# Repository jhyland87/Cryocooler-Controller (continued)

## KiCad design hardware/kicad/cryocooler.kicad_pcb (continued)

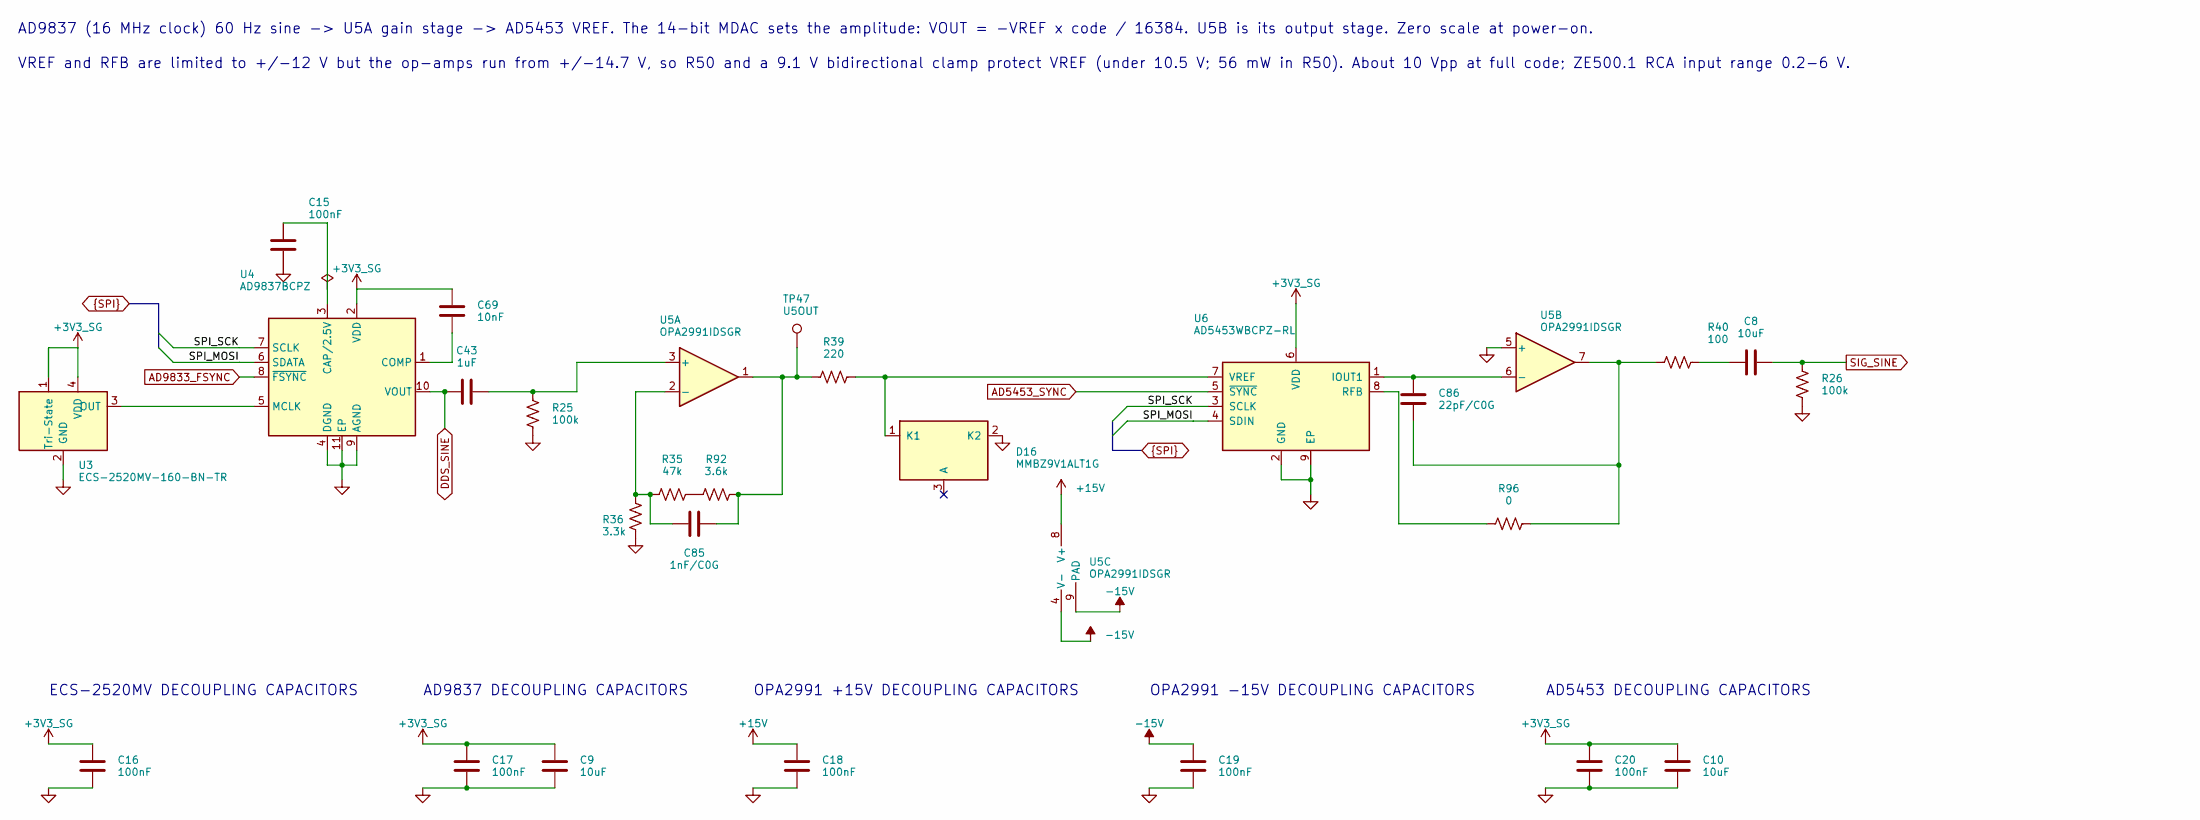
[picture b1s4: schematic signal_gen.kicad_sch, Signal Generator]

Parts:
C8, C9, C10: 10uF; C_0805_2012Metric
C15, C16, C17, C18, C19, C20: 100nF; C_0402_1005Metric
C43: 1uF; C_0603_1608Metric
C69: 10nF; C_0402_1005Metric
C85: 1nF/C0G; C_0402_1005Metric
C86: 22pF/C0G; C_0402_1005Metric
D16: MMBZ9V1ALT1G; SOT-23
R25, R26: 100k; R_0402_1005Metric
R35: 47k; R_0402_1005Metric
R36: 3.3k; R_0402_1005Metric
R39: 220; R_0402_1005Metric
R40: 100; R_0402_1005Metric
R92: 3.6k; R_1206_or_Bourns_3313J
R96: 0; R_1206_or_Bourns_3313J
TP47: U5OUT; TestPoint_Pad_D1.0mm
U3: ECS-2520MV-160-BN-TR; Oscillator_SMD_ECS_2520MV-xxx-xx-4Pin_2.5x2.0mm
U4: AD9837BCPZ; LFCSP-WD-10-1EP_3x3mm_P0.5mm_EP1.64x2.38mm
U5: OPA2991IDSGR; TI_DSG0008A_WSON-8-1EP_2x2mm_P0.5mm_EP0.9x1.6mm
U6: AD5453WBCPZ-RL; VSON-8-1EP_3x3mm_P0.65mm_EP1.65x2.4mm

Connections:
+3V3_SG: C9.1, C10.1, C16.1, C17.1, C20.1, C69.1, U3.1 (Tri-State), U3.4 (VDD), U4.2 (VDD), U6.6 (VDD); also elsewhere on the board
+15V: C18.1, U5.8 (V+); also elsewhere on the board
-15V: C19.1, U5.4 (V-), U5.9 (PAD); also elsewhere on the board
AD5453_SYNC: U6.5 (~SYNC); also elsewhere on the board
AD9833_FSYNC: U4.8 (~FSYNC); also elsewhere on the board
DDS_SINE: C43.1, U4.10 (VOUT); also elsewhere on the board
GND: C9.2, C10.2, C15.2, C16.2, C17.2, C18.2, C19.2, C20.2, D16.2 (K2), R25.2, R26.2, R36.2, U3.2 (GND), U4.4 (DGND), U4.9 (AGND), U4.11 (EP), U5.5 (+), U6.2 (GND), U6.9 (EP); also elsewhere on the board
unnamed: C8.1, R40.2
unnamed: C85.2, R39.1, R92.2, TP47.1, U5.1
unnamed: C86.2, R40.1, R96.2, U5.7
unnamed: D16.1 (K1), R39.2, U6.7 (VREF)
unnamed: R35.2, R92.1
unnamed: U3.3 (OUT), U4.5 (MCLK)
unnamed: C15.1, U4.3 (CAP/2.5V)
unnamed: C69.2, U4.1 (COMP)
unnamed: C43.2, R25.1, U5.3 (+)
unnamed: C85.1, R35.1, R36.1, U5.2 (-)
unnamed: C86.1, U5.6 (-), U6.1 (IOUT1)
unnamed: R96.1, U6.8 (RFB)
SIG_SINE: C8.2, R26.1; also elsewhere on the board
SPI_MOSI: U4.6 (SDATA), U6.4 (SDIN); also elsewhere on the board
SPI_SCK: U4.7 (SCLK), U6.3 (SCLK); also elsewhere on the board

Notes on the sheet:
ECS-2520MV DECOUPLING CAPACITORS
OPA2991 +15V DECOUPLING CAPACITORS
OPA2991 -15V DECOUPLING CAPACITORS
AD9837 DECOUPLING CAPACITORS
AD9837 (16 MHz clock) 60 Hz sine -> U5A gain stage -> AD5453 VREF. The 14-bit MDAC sets the amplitude: VOUT = -VREF x code / 16384. U5B is its output stage. Zero scale at power-on.
VREF and RFB are limited to +/-12 V but the op-amps run from +/-14.7 V, so R50 and a 9.1 V bidirectional clamp protect VREF (under 10.5 V; 56 mW in R50). About 10 Vpp at full code; ZE500.1 RCA input range 0.2-6 V.
AD5453 DECOUPLING CAPACITORS

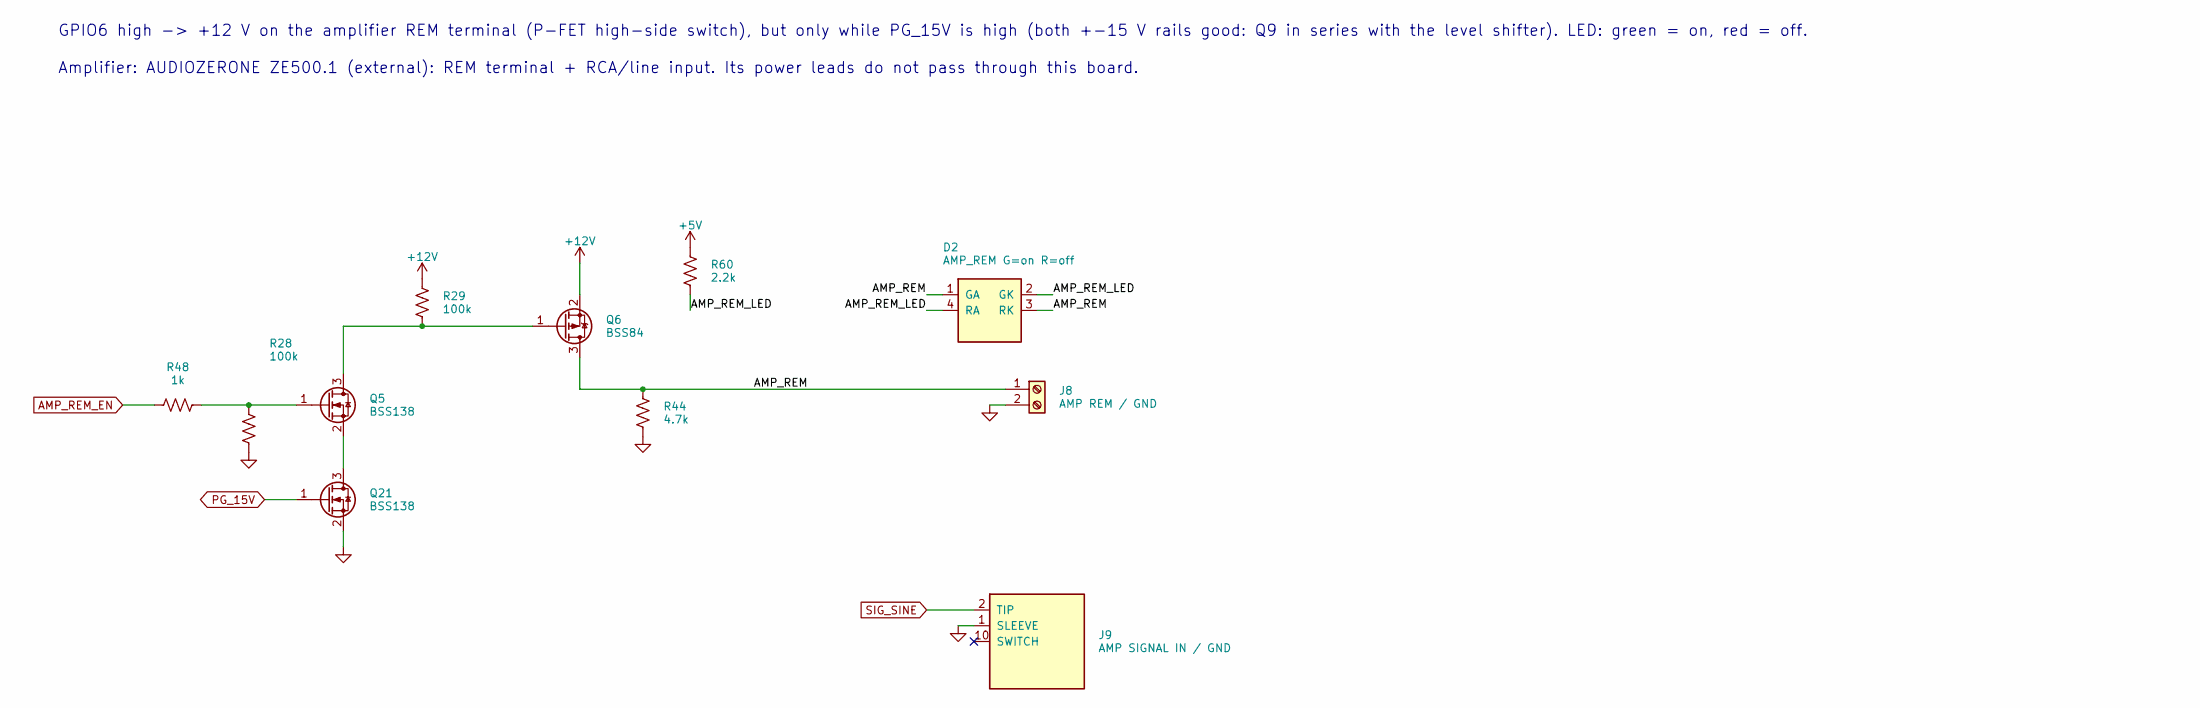
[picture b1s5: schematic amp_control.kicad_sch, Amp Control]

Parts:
D2: AMP_REM G=on R=off; LED_Kingbright_APGB0607
J8: AMP REM / GND; PhoenixContact_MC_0,5_2-G-2,54_SMD_1x02_P2.54mm_Horizontal
J9: AMP SIGNAL IN / GND; SameSky_MJ-3523-SMT-TR_3.5mm_Horizontal_SMD
Q5, Q21: BSS138; SOT-23
Q6: BSS84; SOT-23
R28, R29: 100k; R_0402_1005Metric
R44: 4.7k; R_0402_1005Metric
R48: 1k; R_0402_1005Metric
R60: 2.2k; R_0402_1005Metric

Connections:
+5V: R60.1; also elsewhere on the board
+12V: Q6.2 (S), R29.1; also elsewhere on the board
/Amp Control/AMP_REM: D2.1 (GA), D2.3 (RK), J8.1, Q6.3 (D), R44.1
/Amp Control/AMP_REM_LED: D2.2 (GK), D2.4 (RA), R60.2
AMP_REM_EN: R48.1; also elsewhere on the board
GND: J8.2, J9.1 (SLEEVE), Q21.2 (S), R28.2, R44.2; also elsewhere on the board
unnamed: Q5.3 (D), Q6.1 (G), R29.2
unnamed: Q5.1 (G), R28.1, R48.2
unnamed: Q5.2 (S), Q21.3 (D)
PG_15V: Q21.1 (G); also elsewhere on the board
SIG_SINE: J9.2 (TIP); also elsewhere on the board

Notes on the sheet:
GPIO6 high -> +12 V on the amplifier REM terminal (P-FET high-side switch), but only while PG_15V is high (both +-15 V rails good: Q9 in series with the level shifter). LED: green = on, red = off.
Amplifier: AUDIOZERONE ZE500.1 (external): REM terminal + RCA/line input. Its power leads do not pass through this board.

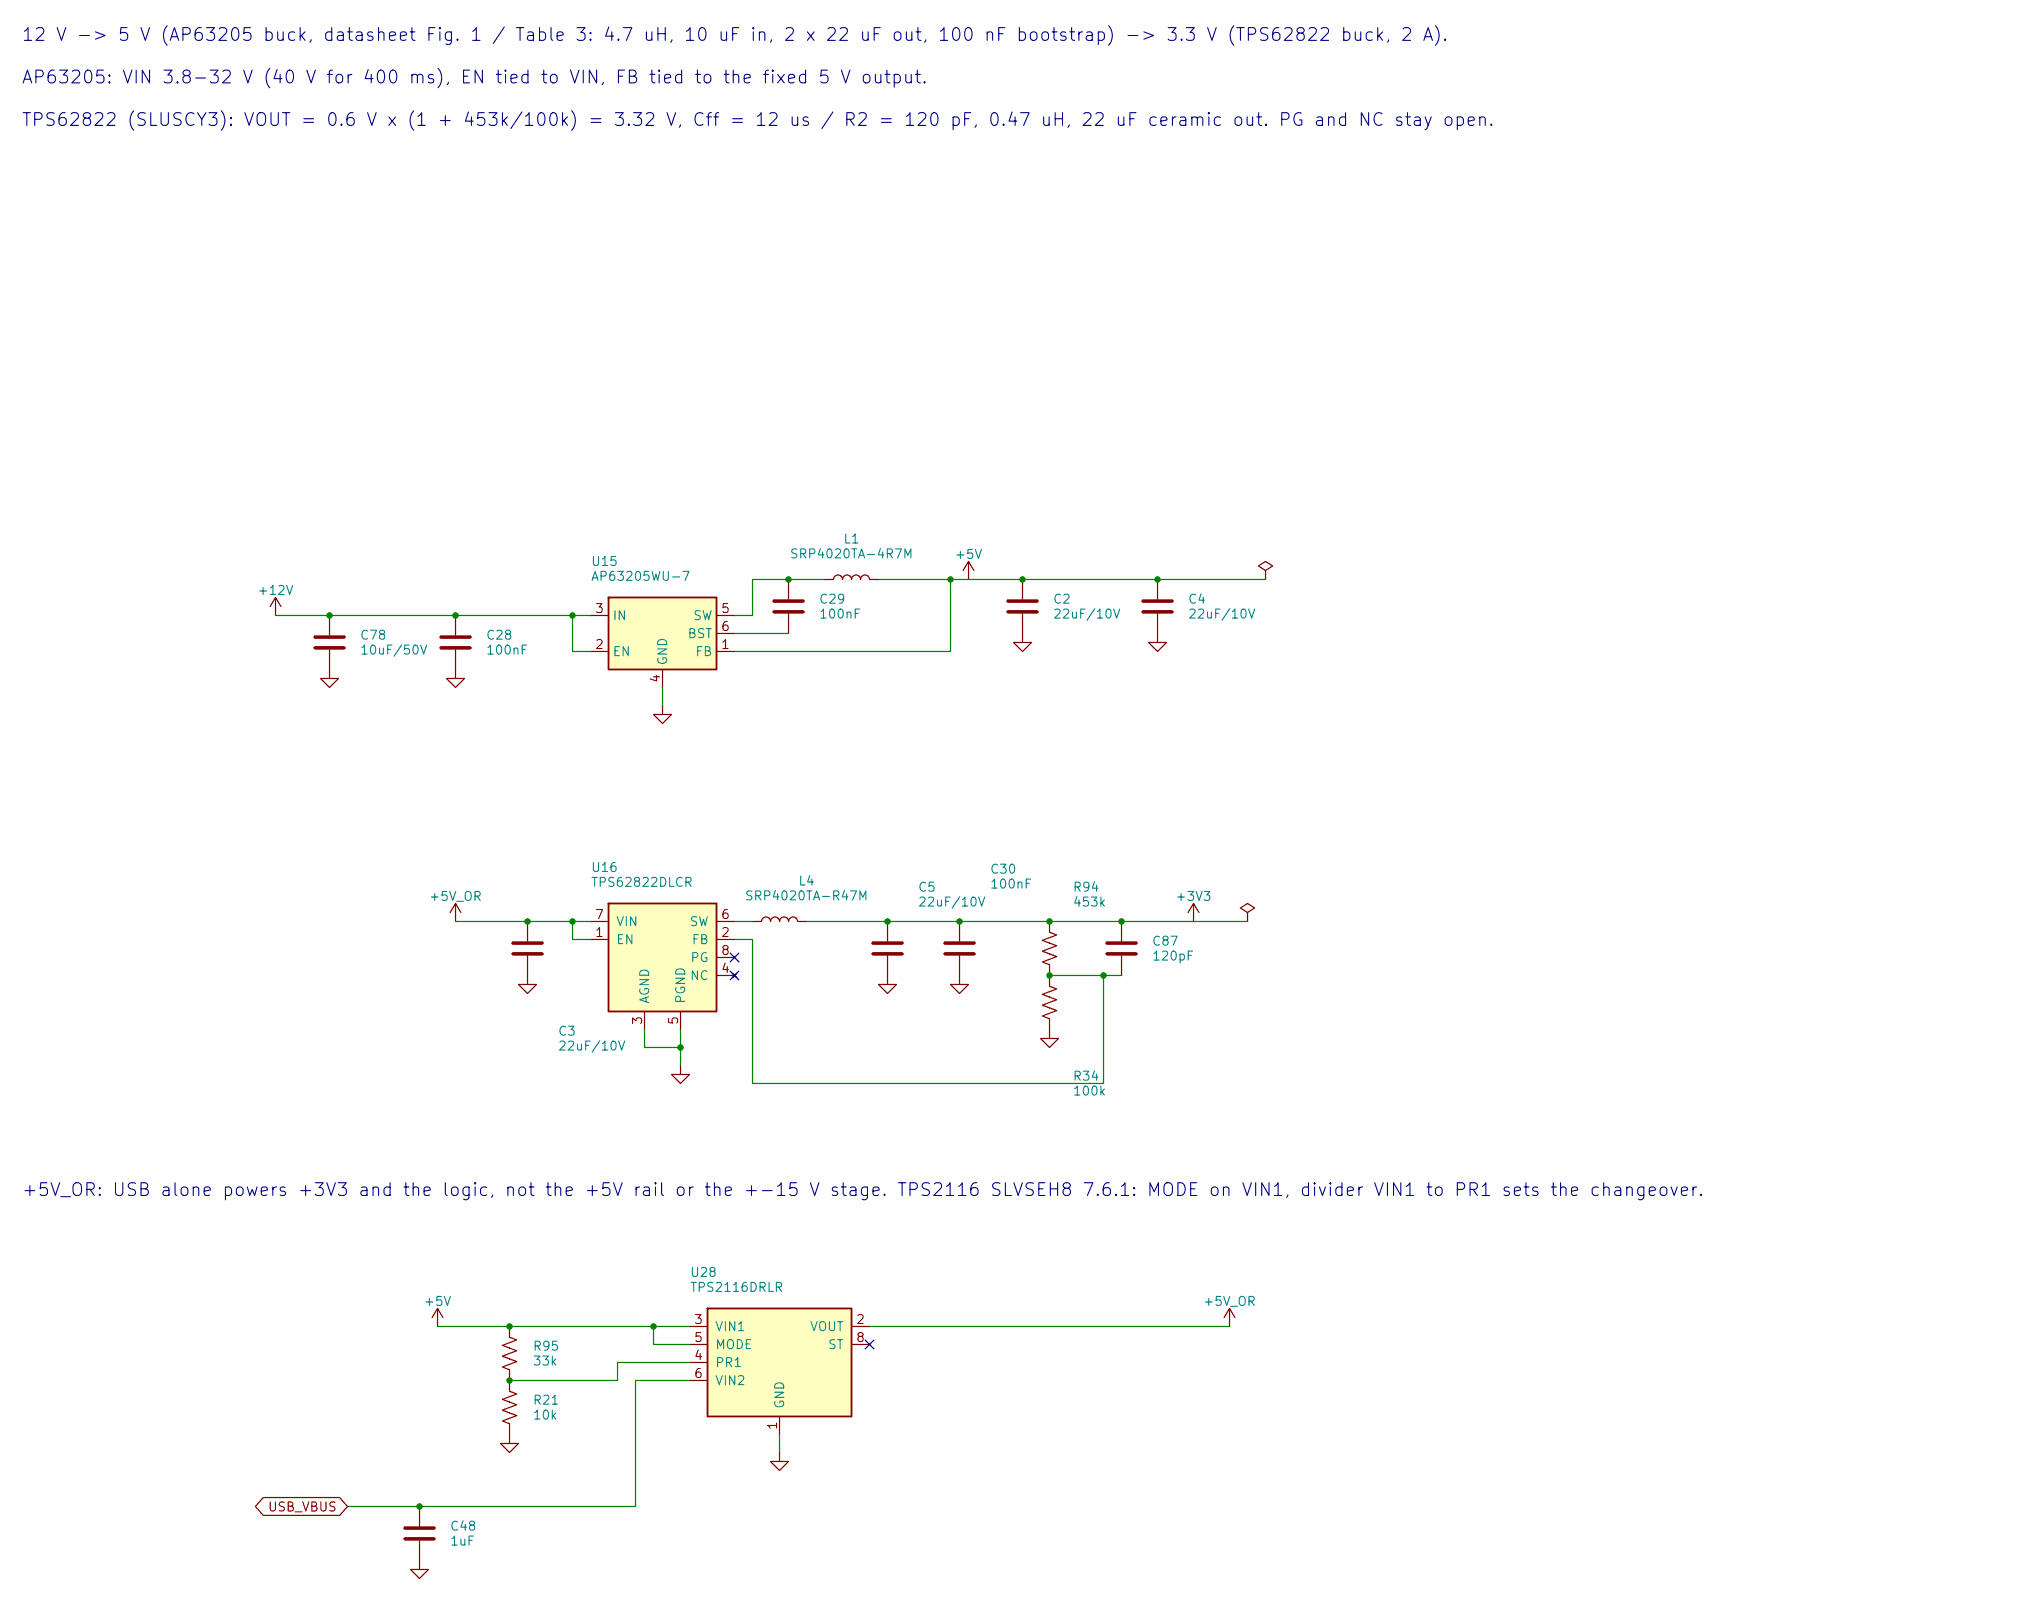
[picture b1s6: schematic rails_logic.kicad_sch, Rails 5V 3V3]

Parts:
C2, C3, C4, C5: 22uF/10V; C_1206_3216Metric
C28, C29, C30: 100nF; C_0402_1005Metric
C48: 1uF; C_0603_1608Metric
C78: 10uF/50V; C_1206_3216Metric
C87: 120pF; C_0402_1005Metric
L1: SRP4020TA-4R7M; L_Bourns_SRP4020TA
L4: SRP4020TA-R47M; L_Bourns_SRP4020TA
R21: 10k; R_0402_1005Metric
R34: 100k; R_0402_1005Metric
R94: 453k; R_0402_1005Metric
R95: 33k; R_0402_1005Metric
U15: AP63205WU-7; TSOT-23-6
U16: TPS62822DLCR; Texas_VSON-HR-8_1.5x2mm_P0.5mm
U28: TPS2116DRLR; SOT-583-8

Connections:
+3V3: C5.1, C30.1, C87.1, L4.2, R94.1; also elsewhere on the board
+5V: C2.1, C4.1, L1.2, R95.1, U15.1 (FB), U28.3 (VIN1), U28.5 (MODE); also elsewhere on the board
+5V_OR: C3.1, U16.1 (EN), U16.7 (VIN), U28.2 (VOUT), U28.7 (VOUT); also elsewhere on the board
+12V: C28.1, C78.1, U15.2 (EN), U15.3 (IN); also elsewhere on the board
GND: C2.2, C3.2, C4.2, C5.2, C28.2, C30.2, C48.2, C78.2, R21.2, R34.2, U15.4 (GND), U16.3 (AGND), U16.5 (PGND), U28.1 (GND); also elsewhere on the board
unnamed: C29.2, U15.6 (BST)
unnamed: C29.1, L1.1, U15.5 (SW)
unnamed: C87.2, R34.1, R94.2, U16.2 (FB)
unnamed: L4.1, U16.6 (SW)
unnamed: R21.1, R95.2, U28.4 (PR1)
USB_VBUS: C48.1, U28.6 (VIN2); also elsewhere on the board

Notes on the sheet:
12 V -> 5 V (AP63205 buck, datasheet Fig. 1 / Table 3: 4.7 uH, 10 uF in, 2 x 22 uF out, 100 nF bootstrap) -> 3.3 V (TPS62822 buck, 2 A).
+5V_OR: USB alone powers +3V3 and the logic, not the +5V rail or the +-15 V stage. TPS2116 SLVSEH8 7.6.1: MODE on VIN1, divider VIN1 to PR1 sets the changeover.
TPS62822 (SLUSCY3): VOUT = 0.6 V x (1 + 453k/100k) = 3.32 V, Cff = 12 us / R2 = 120 pF, 0.47 uH, 22 uF ceramic out. PG and NC stay open.
AP63205: VIN 3.8-32 V (40 V for 400 ms), EN tied to VIN, FB tied to the fixed 5 V output.

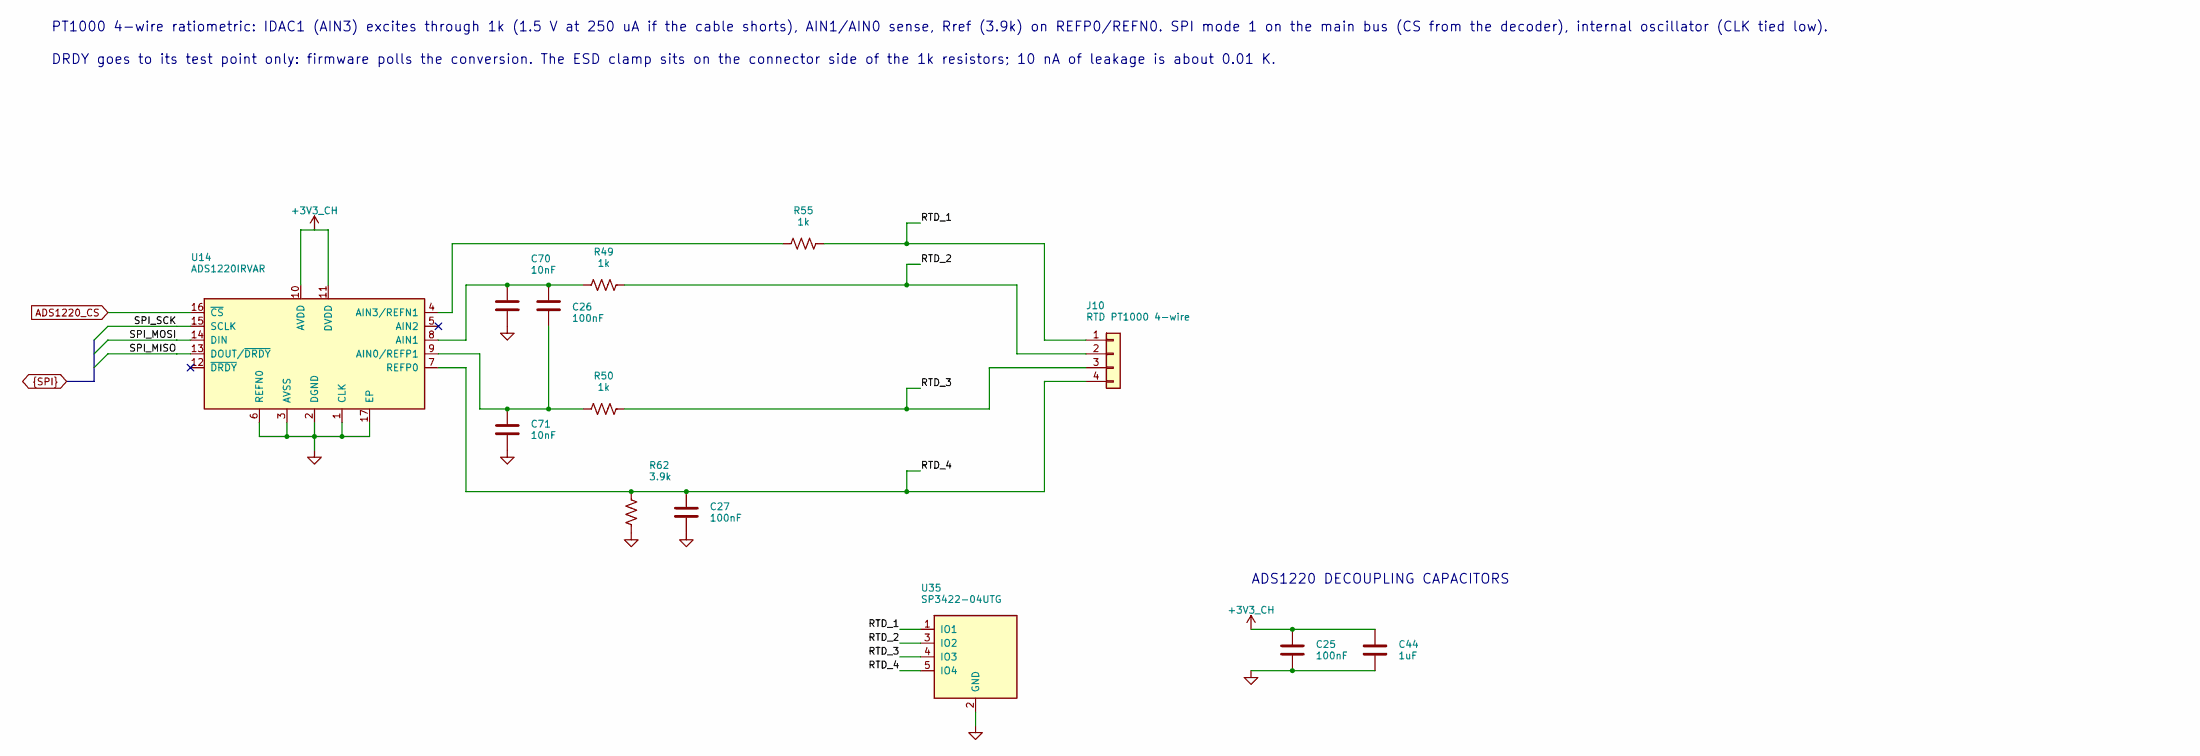
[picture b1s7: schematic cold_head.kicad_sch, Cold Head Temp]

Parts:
C25, C26, C27: 100nF; C_0402_1005Metric
C44: 1uF; C_0603_1608Metric
C70, C71: 10nF; C_0402_1005Metric
J10: RTD PT1000 4-wire; Adafruit_4392_JST-PH_1x04_P2.00mm_Horizontal_SMD
R49, R50, R55: 1k; R_0402_1005Metric
R62: 3.9k; R_0402_1005Metric
U14: ADS1220IRVAR; Texas_RVA_VQFN-16-1EP_3.5x3.5mm_P0.5mm_EP2.14x2.14mm
U35: SP3422-04UTG; Littelfuse_DFN-5_1.0x0.6mm_P0.35mm

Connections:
+3V3_CH: C25.1, C44.1, U14.10 (AVDD), U14.11 (DVDD); also elsewhere on the board
/Cold Head Temp/RTD_1: J10.1, R55.2, U35.1 (IO1)
/Cold Head Temp/RTD_2: J10.2, R49.2, U35.3 (IO2)
/Cold Head Temp/RTD_3: J10.3, R50.2, U35.4 (IO3)
/Cold Head Temp/RTD_4: C27.1, J10.4, R62.1, U14.7 (REFP0), U35.5 (IO4)
ADS1220_CS: U14.16 (~CS); also elsewhere on the board
GND: C25.2, C27.2, C44.2, C70.2, C71.2, R62.2, U14.1 (CLK), U14.2 (DGND), U14.3 (AVSS), U14.6 (REFN0), U14.17 (EP), U35.2 (GND); also elsewhere on the board
unnamed: C26.2, C71.1, R50.1, U14.9 (AIN0/REFP1)
unnamed: C26.1, C70.1, R49.1, U14.8 (AIN1)
unnamed: R55.1, U14.4 (AIN3/REFN1)
SPI_MISO: U14.13 (DOUT/~DRDY); also elsewhere on the board
SPI_MOSI: U14.14 (DIN); also elsewhere on the board
SPI_SCK: U14.15 (SCLK); also elsewhere on the board

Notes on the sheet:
PT1000 4-wire ratiometric: IDAC1 (AIN3) excites through 1k (1.5 V at 250 uA if the cable shorts), AIN1/AIN0 sense, Rref (3.9k) on REFP0/REFN0. SPI mode 1 on the main bus (CS from the decoder), internal oscillator (CLK tied low).
DRDY goes to its test point only: firmware polls the conversion. The ESD clamp sits on the connector side of the 1k resistors; 10 nA of leakage is about 0.01 K.
ADS1220 DECOUPLING CAPACITORS

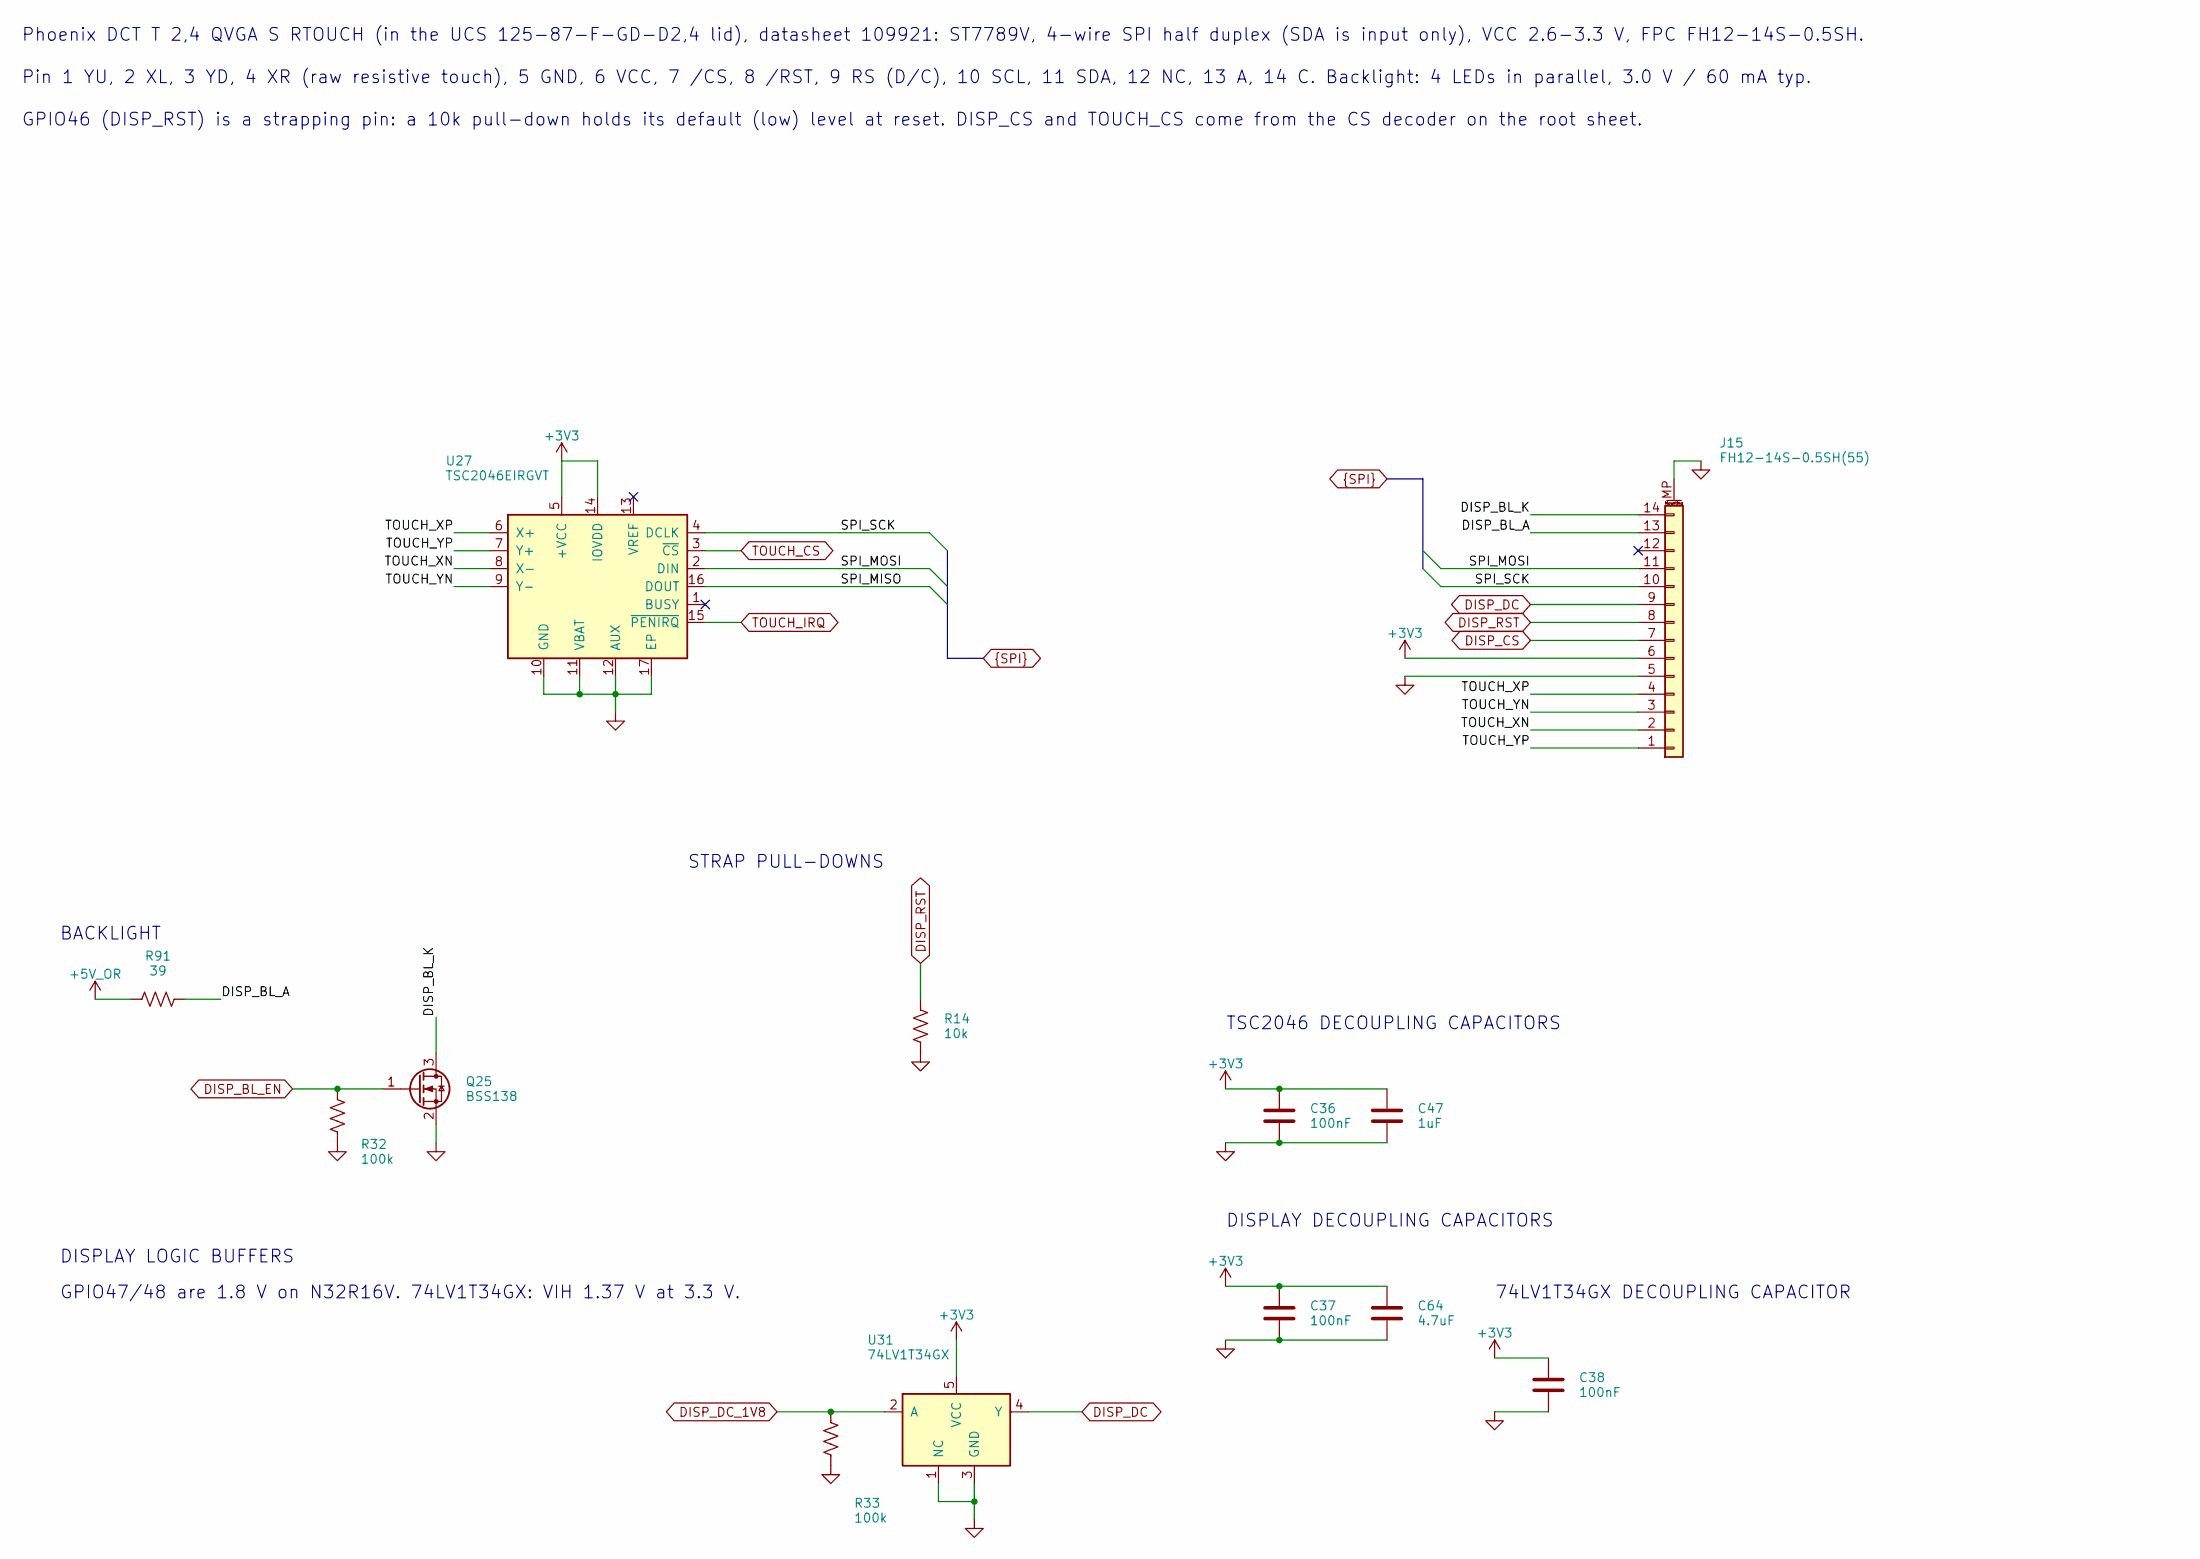
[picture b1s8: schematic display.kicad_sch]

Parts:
C36, C37, C38: 100nF; C_0402_1005Metric
C47: 1uF; C_0603_1608Metric
C64: 4.7uF; C_0805_2012Metric
J15: FH12-14S-0.5SH(55); Hirose_FH12-14S-0.5SH_1x14-1MP_P0.50mm_Horizontal
Q25: BSS138; SOT-23
R14: 10k; R_0402_1005Metric
R32, R33: 100k; R_0402_1005Metric
R91: 39; R_1206_3216Metric
U27: TSC2046EIRGVT; Texas_RGV0016A_VQFN-16-1EP_4x4mm_P0.65mm_EP2.1x2.1mm
U31: 74LV1T34GX; Nexperia_X2SON-5_SOT1226-3_0.8x0.8mm_P0.5mm

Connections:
+3V3: C36.1, C37.1, C38.1, C47.1, C64.1, J15.6, U27.5 (+VCC), U27.14 (IOVDD), U31.5 (VCC); also elsewhere on the board
+5V_OR: R91.1; also elsewhere on the board
/Display/DISP_BL_A: J15.13, R91.2
/Display/DISP_BL_K: J15.14, Q25.3 (D)
/Display/TOUCH_XN: J15.2, U27.8 (X-)
/Display/TOUCH_XP: J15.4, U27.6 (X+)
/Display/TOUCH_YN: J15.3, U27.9 (Y-)
/Display/TOUCH_YP: J15.1, U27.7 (Y+)
DISP_BL_EN: Q25.1 (G), R32.1; also elsewhere on the board
DISP_CS: J15.7; also elsewhere on the board
DISP_DC: J15.9, U31.4 (Y)
DISP_DC_1V8: R33.1, U31.2 (A); also elsewhere on the board
DISP_RST: J15.8, R14.1; also elsewhere on the board
GND: C36.2, C37.2, C38.2, C47.2, C64.2, J15.5, J15.MP (MountPin), Q25.2 (S), R14.2, R32.2, R33.2, U27.10 (GND), U27.11 (VBAT), U27.12 (AUX), U27.17 (EP), U31.1 (NC), U31.3 (GND); also elsewhere on the board
SPI_MISO: U27.16 (DOUT); also elsewhere on the board
SPI_MOSI: J15.11, U27.2 (DIN); also elsewhere on the board
SPI_SCK: J15.10, U27.4 (DCLK); also elsewhere on the board
TOUCH_CS: U27.3 (~CS); also elsewhere on the board
TOUCH_IRQ: U27.15 (~PENIRQ); also elsewhere on the board

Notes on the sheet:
DISPLAY LOGIC BUFFERS
Phoenix DCT T 2,4 QVGA S RTOUCH (in the UCS 125-87-F-GD-D2,4 lid), datasheet 109921: ST7789V, 4-wire SPI half duplex (SDA is input only), VCC 2.6-3.3 V, FPC FH12-14S-0.5SH.
GPIO47/48 are 1.8 V on N32R16V. 74LV1T34GX: VIH 1.37 V at 3.3 V.
BACKLIGHT
GPIO46 (DISP_RST) is a strapping pin: a 10k pull-down holds its default (low) level at reset. DISP_CS and TOUCH_CS come from the CS decoder on the root sheet.
DISPLAY DECOUPLING CAPACITORS
74LV1T34GX DECOUPLING CAPACITOR
TSC2046 DECOUPLING CAPACITORS
Pin 1 YU, 2 XL, 3 YD, 4 XR (raw resistive touch), 5 GND, 6 VCC, 7 /CS, 8 /RST, 9 RS (D/C), 10 SCL, 11 SDA, 12 NC, 13 A, 14 C. Backlight: 4 LEDs in parallel, 3.0 V / 60 mA typ.
STRAP PULL-DOWNS

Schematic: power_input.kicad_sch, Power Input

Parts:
C65: 100uF/35V; CP_Elec_8x10
C67: 100nF; C_0805_2012Metric
D1: SMBJ16A; D_SMB
F1: 5A backup; Fuse_Littelfuse-NANO2-451_453
J2: 12V IN; Tensility_54-00164_5.5x2.1mm_Horizontal_SMD

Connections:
GND: C65.2, C67.2, D1.2 (A2), J2.2, J2.3; also elsewhere on the board
unnamed: F1.1, J2.1
VIN: C65.1, C67.1, D1.1 (A1), F1.2; also elsewhere on the board

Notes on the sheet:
F1 is a backup only: add an inline high-breaking-capacity fuse (7.5-10 A) at the PSU end. Reverse polarity: TVS forward-clamps and blows the fuse.
12 V input from a Dell XYK93 (DPS-2000EB class, ~12.2 V, ~160 A available): use the main 12 V rail with PS_ON held low.

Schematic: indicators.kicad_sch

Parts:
C33, C34: 100nF; C_0402_1005Metric
D13: WS2812B-2020; LED_WS2812B-2020_PLCC4_2.0x2.0mm
R10: 10k; R_0402_1005Metric
R85: 330; R_0402_1005Metric
U24: 74AHCT1G125GM; Nexperia_XSON-6_SOT886_1.0x1.45mm_P0.5mm

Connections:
+5V: C33.1, C34.1, D13.4 (VDD), U24.6 (VCC); also elsewhere on the board
GND: C33.2, C34.2, D13.2 (VSS), R10.2, U24.1 (~OE), U24.3 (GND); also elsewhere on the board
unnamed: D13.3 (DIN), R85.2
unnamed: R85.1, U24.4 (Y)
STATUS_RGB: R10.1, U24.2 (A); also elsewhere on the board

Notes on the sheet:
WS2812B-2020 status LED on GPIO38 via a 74AHCT1G125GM 3.3 V -> 5 V level shifter. Works without the SPI bus, so it can show faults the bus would hide.
74AHCT1G125GM DECOUPLING CAPACITORS
WS2812B-2020 DECOUPLING CAPACITORS

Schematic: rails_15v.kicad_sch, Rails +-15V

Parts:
C11, C12: 10uF; C_0805_2012Metric
C40: 100nF; C_0402_1005Metric
C49, C50: 1uF; C_0603_1608Metric
C55: 68nF; C_0603_1608Metric
C56, C57, C58, C59, C60, C61, C62: 22uF/25V X7R; C_1210_3225Metric
C79: 47nF; C_0603_1608Metric
C81, C82: 1uF/50V; C_1206_3216Metric
D4, D5: DFLS240; D_PowerDI-123
L2: SRP7050TA-3R3M; L_Bourns_SRP7050TA
L3: SRP7050TA-6R8M; L_Bourns_SRP7050TA
R11, R12: 10k; R_0402_1005Metric
R68: 5.6k; R_0402_1005Metric
R69: 12k; R_0402_1005Metric
R70: 2.67M; R_0402_1005Metric
R71: 137k; R_0402_1005Metric
R72: 2.55M; R_0402_1005Metric
R73: 118k; R_0402_1005Metric
R74, R75: 432k; R_0402_1005Metric
R76, R77: 147k; R_0402_1005Metric
U20: ADP5071ACPZ; LFCSP-20-1EP_4x4mm_P0.5mm_EP2.5x2.5mm
U21: LT3097ADJC; DFN-22-2EP_6x3mm_P0.5mm_LT3097

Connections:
+5V_PS15: C11.1, C12.1, C40.1, U20.7 (EN1), U20.9 (EN2), U20.15 (PVIN1), U20.16 (PVINSYS), U20.17 (PVIN2); also elsewhere on the board
+15V: C57.1, C59.1, R74.1, U21.20 (OUTSP), U21.21 (OUTP), U21.22 (OUTP); also elsewhere on the board
+16V5: C56.1, D4.1 (K), R70.1, U21.1 (INP), U21.2 (INP), U21.3 (ENP/UVP); also elsewhere on the board
-15V: C58.1, C60.1, R75.1, U21.14 (OUTSN), U21.15 (OUTN), U21.16 (OUTN); also elsewhere on the board
-16V5: C61.1, C62.1, D5.2 (A), R72.1, U21.6 (INN), U21.7 (INN), U21.8 (ENN/UVN), U21.24 (INN); also elsewhere on the board
GND: C11.2, C12.2, C40.2, C49.2, C50.2, C55.2, C56.2, C57.2, C58.2, C59.2, C60.2, C61.2, C62.2, C79.2, C81.2, C82.2, L3.2, R11.2, R12.2, R71.2, R76.2, R77.2, U20.2 (SYNC), U20.4 (SLEW), U20.13 (AGND), U20.19 (PGND), U20.21 (EP), U21.5 (ILIMP), U21.11 (ILIMN), U21.13 (GND), U21.19 (GND), U21.23 (GND); also elsewhere on the board
unnamed: C55.1, R69.1
unnamed: C79.1, R68.1
unnamed: D4.2 (A), L2.2, U20.20 (SW1)
unnamed: D5.1 (K), L3.1, U20.18 (SW2)
unnamed: R68.2, U20.6 (COMP1)
unnamed: R69.2, U20.10 (COMP2)
unnamed: R70.2, R71.1, U20.5 (FB1)
unnamed: R72.2, R73.1, U20.11 (FB2)
unnamed: L2.1, U20.1 (INBK)
unnamed: C49.1, U20.3 (SEQ), U20.14 (VREG)
unnamed: C50.1, R73.2, U20.12 (VREF)
unnamed: R12.1, R75.2, U21.10 (PGFBN)
unnamed: R11.1, R74.2, U21.17 (PGFBP)
unnamed: C82.1, R77.1, U21.12 (SETN)
unnamed: C81.1, R76.1, U21.18 (SETP)
PGN_15V: U21.9 (PGN); also elsewhere on the board
PGP_15V: U21.4 (PGP); also elsewhere on the board

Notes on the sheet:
ADP5071 DECOUPLING CAPACITORS
ADP5071 layout: keep PGND off the exposed pad on the top layer (datasheet layout section). SEQ on VREG starts both channels together when EN2 rises.
ADP5071ACPZ (5 V in): +16.4 V boost and -16.5 V inverting rails; one LT3097 post-regulates them to +/-14.7 V.
ADP5071 values from datasheet Fig. 47 / Tables 9-11. LT3097: VOUT = 100 uA x RSET (147k = 14.7 V, +15 V is the top of its range); PGFB dividers 432k/10k trip power good near 13.3 V (also enables fast start-up).

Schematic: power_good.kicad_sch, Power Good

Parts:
D11: PG +15V G=good R=bad; LED_Kingbright_APGB0607
D12: PG -15V G=good R=bad; LED_Kingbright_APGB0607
D15: BAT54AW; SOT-323_SC-70
Q22, Q23, Q24, Q51, Q52: BSS138; SOT-323_SC-70
Q42: BSS138W; SOT-323_SC-70
R13: 10k; R_0402_1005Metric
R52: 1k; R_0402_1005Metric
R57, R58: 220k; R_0402_1005Metric
R83, R84: 2.2k; R_0402_1005Metric
R86, R87: 62k; R_0402_1005Metric
R88, R89, R90: 470k; R_0402_1005Metric
R402, R404: 100k; R_0402_1005Metric
R403, R405: 1.5k; R_0402_1005Metric

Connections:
+3V3: R13.1, R88.2, R402.1, R403.1, R404.1, R405.1; also elsewhere on the board
+5V: R83.1, R84.1; also elsewhere on the board
+15V: R57.1, R58.1, R89.1; also elsewhere on the board
-15V: R90.2; also elsewhere on the board
/Power Good/PGN_LED_GA: D12.1 (GA), R84.2
/Power Good/PGN_LED_GK: D12.2 (GK), Q24.3 (D), Q52.1 (G), R404.2
/Power Good/PGN_LED_RA: D12.4 (RA), R405.2
/Power Good/PGN_LED_RK: D12.3 (RK), Q52.3 (D)
/Power Good/PGP_LED_GA: D11.1 (GA), R83.2
/Power Good/PGP_LED_GK: D11.2 (GK), Q23.3 (D), Q51.1 (G), R402.2
/Power Good/PGP_LED_RA: D11.4 (RA), R403.2
/Power Good/PGP_LED_RK: D11.3 (RK), Q51.3 (D)
GND: Q22.2 (S), Q23.2 (S), Q24.2 (S), Q42.2 (S), Q51.2 (S), Q52.2 (S), R86.2, R87.2; also elsewhere on the board
unnamed: Q22.3 (D), R13.2, R52.1
unnamed: Q42.1 (G), R89.2, R90.1
PGN_15V: D15.2, Q24.1 (G), Q42.3 (D), R58.2, R87.1; also elsewhere on the board
PGP_15V: D15.1, Q23.1 (G), R57.2, R86.1; also elsewhere on the board
PG_15V: D15.3, Q22.1 (G), R88.1; also elsewhere on the board
PG_15V_N: R52.2; also elsewhere on the board

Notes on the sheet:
-15 V GUARD: an unpowered LT3097 cannot pull PGN low. Midpoint near 0 V with both rails up, about +7.5 V with -15 V missing.
PGP and PGN pull their own node low when bad. Each node is the +15 V rail through 220k/62k (about 3.2 V when good, under 0.3 V if its pin pulls low or the rail is missing) and lights its LED green, or red when low.
PG_15V = the two nodes ANDed by a BAT54AW with a 470k pull-up to +3V3 (weak so it cannot lift dead nodes; 3.3 V only when both are good); it gates the amplifier REM switch and reads LOW on GPIO43 (PG_15V_N) when both rails are good.

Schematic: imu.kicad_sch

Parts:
J14: 505448-0891; Molex_Micro-Lock_Plus_505448-0891_2x04_P1.25mm_Horizontal
U36: NUF6401MNT1G; OnSemi_DFN-12-1EP_506AD

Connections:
+3V3: J14.4; also elsewhere on the board
GND: J14.2, U36.13 (GND); also elsewhere on the board
IMU_CS: U36.4 (CH4); also elsewhere on the board
IMU_INT1: U36.2 (CH2); also elsewhere on the board
IMU_INT2: U36.1 (CH1); also elsewhere on the board
unnamed: J14.1, U36.7 (CH6)
unnamed: J14.3, U36.8 (CH5)
unnamed: J14.5, U36.9 (CH4)
unnamed: J14.6, U36.10 (CH3)
unnamed: J14.7, U36.11 (CH2)
unnamed: J14.8, U36.12 (CH1)
SPI_MISO: U36.3 (CH3); also elsewhere on the board
SPI_MOSI: U36.5 (CH5); also elsewhere on the board
SPI_SCK: U36.6 (CH6); also elsewhere on the board

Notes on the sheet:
Module Vin = +3V3 keeps its logic at 3.3 V. NUF6401MN filter: 100 R in series to damp the cable, 17 pF and an ESD clamp on each side of all six signals.
LSM6DSOX is the off-board Adafruit module (product 4438) on the cooler, cabled to J14 (Molex Micro-Lock Plus 2x4, 1.25 mm) over the main SPI bus (CS from the decoder, INT1 GPIO2 single-tap, INT2 GPIO39 wake-up).
J14 pin -> module pad: 1 SCL, 2 GND, 3 SDA, 4 Vin, 5 CS, 6 DO, 7 I1, 8 I2 (3Vo pad open). Keep the cable short and twist SCK with GND (pins 1-2 sit one above the other).

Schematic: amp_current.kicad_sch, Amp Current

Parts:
C6, C7: 22uF/10V; C_1206_3216Metric
C31, C301, C302: 100nF; C_0402_1005Metric
C45, C51, C52, C53, C54: 1uF; C_0603_1608Metric
C72, C73, C74, C75: 10nF; C_0402_1005Metric
FB1, FB2: BLM15EX331SN1D; L_0402_1005Metric
J11: AMP OUT (+ / -); TE_2305908-2_1x02_P5.00mm_Horizontal_SMD
J12: CRYOCOOLER (+ / - / GND); TE_643228-1_1x03_P6.35mm_Horizontal
R22, R501, R502: 10k; R_0402_1005Metric
R63: 4.02k; R_0603_1608Metric
R64, R65, R66, R67: 1M; R_1206_3216Metric
U17: ISOW7741DFMR; TI_DFM0020A
U18: ACS37800KMACTR-015B5-SPI; SOIC-16W_7.5x10.3mm_P1.27mm
U41, U42: SN74LVC1G125DRYR; Texas_USON-6_1x1.45mm_P0.5mm_SMD

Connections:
+3V3: C51.1, C72.1, C301.1, C302.1, R22.1, R501.1, R502.1, U17.1 (VIO), U17.7 (EN_IO1), U41.6 (VCC), U42.6 (VCC); also elsewhere on the board
+5V_ISO: C6.1, C52.1, C73.1, U17.9 (VDD); also elsewhere on the board
ACS_CS: R502.2, U17.4 (INC), U41.1 (~OE), U42.1 (~OE); also elsewhere on the board
ACS_MISO: U17.5 (OUTD), U42.2 (A)
ACS_SCK: R501.2, U17.3 (INB), U41.4 (Y)
GND: C6.2, C51.2, C52.2, C72.2, C73.2, C301.2, C302.2, J12.3, U17.6 (GNDIO), U17.10 (GND1), U41.3 (GND), U42.3 (GND); also elsewhere on the board
ISO_5V: C31.1, C45.1, C54.1, C75.1, FB1.2, U17.14 (EN_IO2), U17.20 (VISOIN), U18.13 (VCC); also elsewhere on the board
ISO_GND: C31.2, C45.2, C54.2, C75.2, FB2.1, J11.2, J12.2, R63.2, U17.15 (GISOIN), U18.14 (GND), U18.15 (VINN); also elsewhere on the board
ISO_GND2: C7.2, C53.2, C74.2, FB2.2, U17.11 (GND2)
unnamed: J11.1, U18.1 (IP+), U18.2 (IP+), U18.3 (IP+), U18.4 (IP+)
unnamed: J12.1, R67.2, U18.5 (IP-), U18.6 (IP-), U18.7 (IP-), U18.8 (IP-)
unnamed: R64.2, R65.1
unnamed: R65.2, R66.1
unnamed: R66.2, R67.1
unnamed: R22.2, U17.8 (EN/FLT)
unnamed: U17.16 (IND), U18.12 (MISO)
unnamed: U17.19 (OUTA), U18.10 (MOSI)
unnamed: U17.18 (OUTB), U18.11 (SCLK)
unnamed: U17.17 (OUTC), U18.9 (~CS)
unnamed: R63.1, R64.1, U18.16 (VINP)
SPI_MISO: U42.4 (Y); also elsewhere on the board
SPI_MOSI: U17.2 (INA); also elsewhere on the board
SPI_SCK: U41.2 (A); also elsewhere on the board
VISOOUT: C7.1, C53.1, C74.1, FB1.1, U17.12 (VISOOUT), U17.13 (VSEL)

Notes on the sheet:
ACS37800 and ISOW7741 drive MISO all the time, so MISO reaches the shared bus only while ACS_CS is low.
ISOW7741 VISOOUT DECOUPLING
Amplifier output V/I monitor: ACS37800 (SPI) on an isolated 5 V domain from the ISOW7741 (110 mA max at 5 V to 5 V; VSEL on VISOOUT selects 5 V). Beads on VISOOUT-VISOIN and GND2-GISOIN follow the ISOW774x datasheet for emissions.
ISOW7741 VIO DECOUPLING
ACS37800 DECOUPLING CAPACITORS
ISOW7741 VDD DECOUPLING
SN74LVC1G125 DECOUPLING CAPACITORS
SCK is gated the same way, so bus traffic for other devices never clocks the ACS37800. 10k pull-ups hold both gates closed at reset.
ACS37800 SPI GATES (LOGIC SIDE)
Mains-class creepage/clearance applies between ISO_GND domain and the logic side on the PCB. EN/FLT is an open-drain fault flag as well as the enable, so it has a pull-up rather than a tie to VIO.
ISOW7741 VISOIN DECOUPLING
